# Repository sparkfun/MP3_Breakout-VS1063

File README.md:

SparkFun MP3 Breakout - VS1063
========================================

[*SparkFun MP3 Breakout - VS1063 (BOB-11684)*](https://www.sparkfun.com/products/11684)

VS1063 is an easy-to-use, versatile encoder, decoder and codec for a multitude of audio formats. 
With this breakout board, it’s easy to drop it into any project. 
The VS1063 is capable of decoding Ogg Vorbis/MP3/AAC/WMA audio and encoding MP3, IMA ADPCM and user-loadable Ogg Vorbis. 
This breakout can also drive 30 ohm headphones with no additional power supply.

Repository Contents
-------------------

* **/Firmware** - Example code 
* **/Hardware** - Eagle design files (.brd, .sch)
* **/Production** - Production panel files (.brd)

Documentation
--------------
* **[SparkFun Fritzing repo](https://github.com/sparkfun/Fritzing_Parts)** - Fritzing diagrams for SparkFun products.
* **[SparkFun 3D Model repo](https://github.com/sparkfun/3D_Models)** - 3D models of SparkFun products. 

License Information
-------------------
This product is _**open source**_! 

The **hardware** is released under [Creative Commons ShareAlike 4.0 International](https://creativecommons.org/licenses/by-sa/4.0/).

The **code** is beerware; if you see me (or any other SparkFun employee) at the local, and you've found our code helpful, please buy us a round!

Please use, reuse, and modify these files as you see fit. Please maintain attribution to SparkFun Electronics and release anything derivative under the same license.

Distributed as-is; no warranty is given.

- Your friends at SparkFun.

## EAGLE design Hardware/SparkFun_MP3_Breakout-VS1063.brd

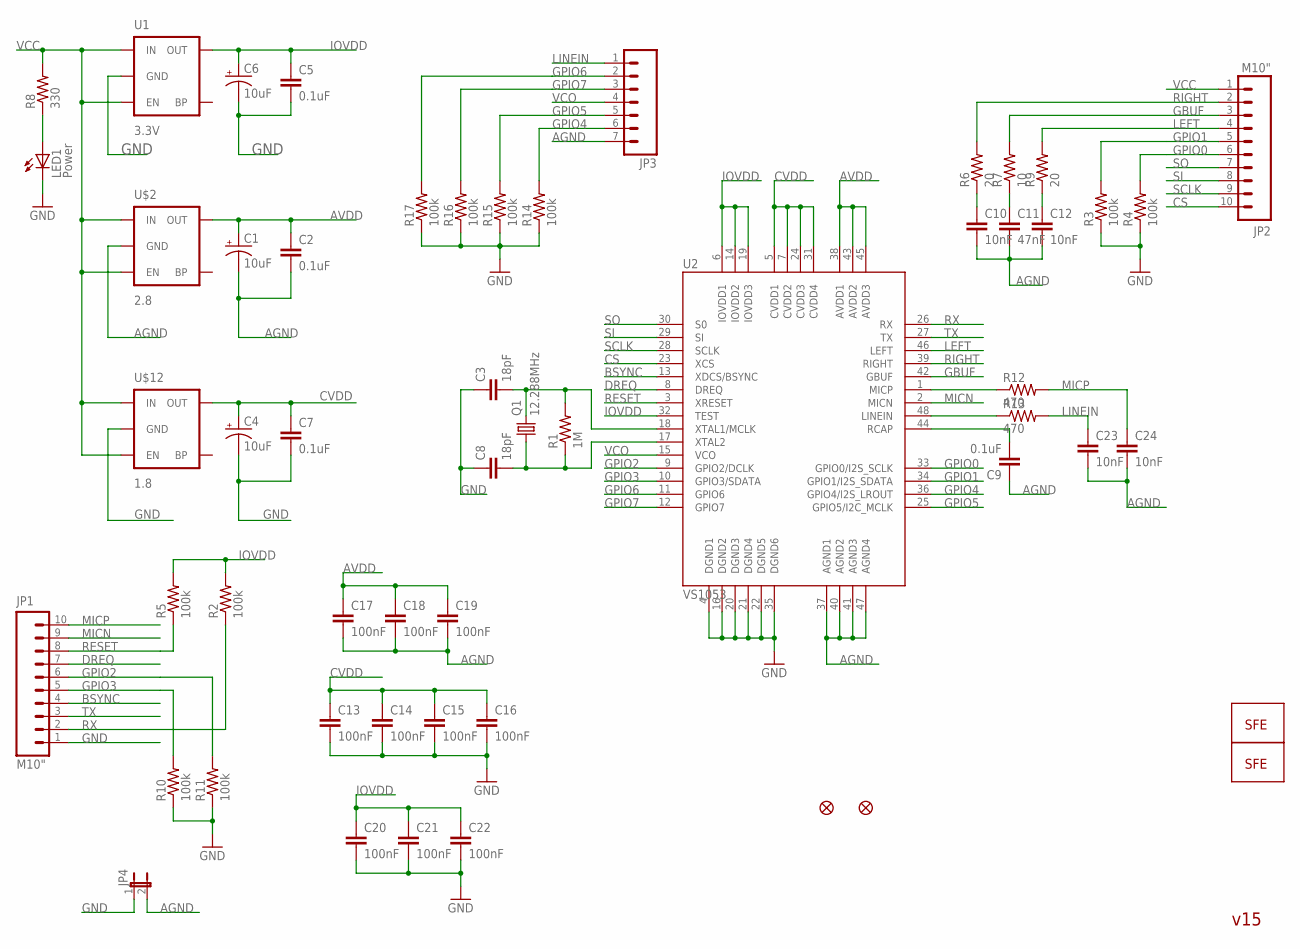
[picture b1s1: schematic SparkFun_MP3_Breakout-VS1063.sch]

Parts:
C1, C4, C6: 10uF; EIA3216
C2, C5, C7, C9: 0.1uF; 0402-CAP
C3, C8: 18pF; 0402-CAP
C10, C12, C23, C24: 10nF; 0402-CAP
C11: 47nF; 0402-CAP
C13, C14, C15, C16, C17, C18, C19, C20, C21, C22: 100nF; 0402-CAP
JP1, JP2: M10"; 1X10
JP3: M07; 1X07
JP4: JUMPER-2SMD-NC; SJ_2S
LED1: Power; LED-0603
Q1: 12.288MHz; CRYSTAL-SMD-5X3
R1: 1M; 0402-RES
R2, R3, R4, R5, R10, R11, R14, R15, R16, R17: 100k; 0402-RES
R6, R9: 20; 0402-RES
R7: 10; 0402-RES
R8: 330; 0402-RES
R12, R13: 470; 0402-RES
U1: 3.3V; SOT23-5
U2: VS1053; LQFP-48
U$2: 2.8; SC70
U$4, U$5: FIDUCIAL1X2; FIDUCIAL-1X2
U$6: LOGO-SFESK; SFE-LOGO-FLAME
U$7: LOGO-SFENEW; SFE-NEW-WEBLOGO
U$12: 1.8; SC70

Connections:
AGND: C1.C (-), C2.2, C9.1, C10.2, C11.2, C12.2, C17.2, C18.2, C19.2, C23.2, C24.2, JP3.7, JP4.2, U2.37 (AGND1), U2.40 (AGND2), U2.41 (AGND3), U2.47 (AGND4), U$2.2 (GND)
AVDD: C1.A (+), C2.1, C17.1, C18.1, C19.1, U2.38 (AVDD1), U2.43 (AVDD2), U2.45 (AVDD3), U$2.5 (OUT)
BSYNC: JP1.4, U2.13 (XDCS/BSYNC)
CS: JP2.10, U2.23 (XCS)
CVDD: C4.A (+), C7.1, C13.1, C14.1, C15.1, C16.1, U2.5 (CVDD1), U2.7 (CVDD2), U2.24 (CVDD3), U2.31 (CVDD4), U$12.5 (OUT)
DREQ: JP1.7, U2.8 (DREQ)
GBUF: JP2.3, R7.2, U2.42 (GBUF)
GND: C3.1, C4.C (-), C5.2, C6.C (-), C7.2, C8.1, C13.2, C14.2, C15.2, C16.2, C20.2, C21.2, C22.2, JP1.1, JP4.1, LED1.C, R3.1, R4.1, R10.1, R11.1, R14.1, R15.1, R16.1, R17.1, U1.2 (GND), U2.4 (DGND1), U2.16 (DGND2), U2.20 (DGND3), U2.21 (DGND4), U2.22 (DGND5), U2.35 (DGND6), U$12.2 (GND)
GPIO0: JP2.6, R4.2, U2.33 (GPIO0/I2S_SCLK)
GPIO1: JP2.5, R3.2, U2.34 (GPIO1/I2S_SDATA)
GPIO2: JP1.6, R11.2, U2.9 (GPIO2/DCLK)
GPIO3: JP1.5, R10.2, U2.10 (GPIO3/SDATA)
GPIO4: JP3.6, R14.2, U2.36 (GPIO4/I2S_LROUT)
GPIO5: JP3.5, R15.2, U2.25 (GPIO5/I2C_MCLK)
GPIO6: JP3.2, R17.2, U2.11 (GPIO6)
GPIO7: JP3.3, R16.2, U2.12 (GPIO7)
IOVDD: C5.1, C6.A (+), C20.1, C21.1, C22.1, R2.2, R5.2, U1.5 (OUT), U2.6 (IOVDD1), U2.14 (IOVDD2), U2.19 (IOVDD3), U2.32 (TEST)
LEFT: JP2.4, R9.2, U2.46 (LEFT)
LINEIN: C23.1, JP3.1, R13.2
MICN: JP1.9, U2.2 (MICN)
MICP: C24.1, JP1.10, R12.2
unnamed: C9.2, U2.44 (RCAP)
unnamed: C12.1, R9.1
unnamed: C10.1, R6.1
unnamed: R12.1, U2.1 (MICP)
unnamed: C11.1, R7.1
unnamed: LED1.A, R8.1
unnamed: R13.1, U2.48 (LINEIN)
unnamed: C3.2, Q1.3 (2), R1.2, U2.18 (XTAL1/MCLK)
unnamed: C8.2, Q1.1, R1.1, U2.17 (XTAL2)
RESET: JP1.8, R5.1, U2.3 (XRESET)
RIGHT: JP2.2, R6.2, U2.39 (RIGHT)
RX: JP1.2, R2.1, U2.26 (RX)
SCLK: JP2.9, U2.28 (SCLK)
SI: JP2.8, U2.29 (SI)
SO: JP2.7, U2.30 (S0)
TX: JP1.3, U2.27 (TX)
VCC: JP2.1, R8.2, U1.1 (IN), U1.3 (EN), U$2.1 (IN), U$2.3 (EN), U$12.1 (IN), U$12.3 (EN)
VCO: JP3.4, U2.15 (VCO)

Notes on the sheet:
v15

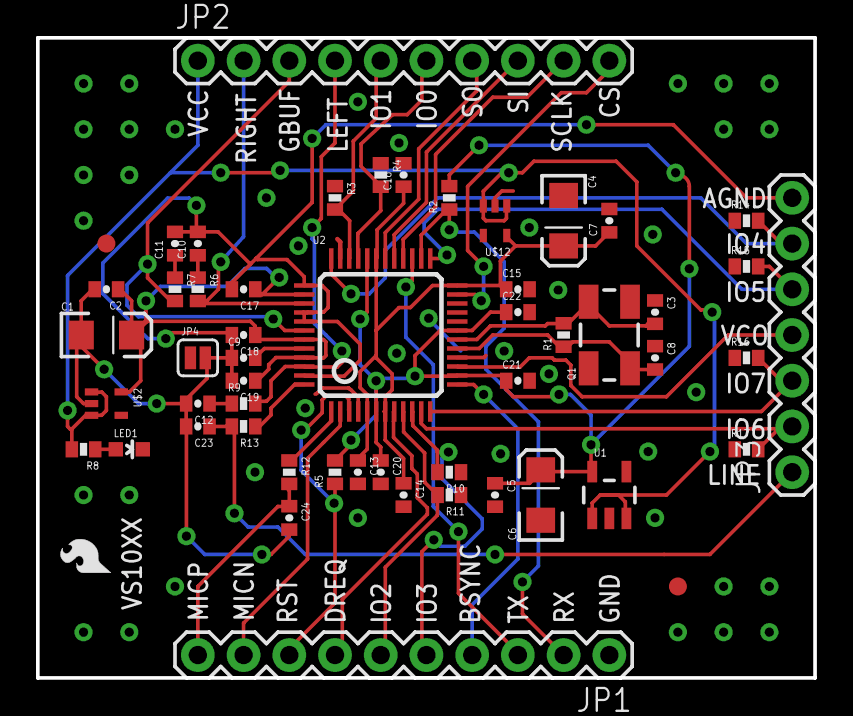
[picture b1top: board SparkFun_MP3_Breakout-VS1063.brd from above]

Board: 2 copper layers, 43.2 x 35.6 mm, 55 parts (1 on the bottom side), 39 nets.

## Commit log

2015-05-11 Adding hardware
